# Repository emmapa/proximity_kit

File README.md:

# Proximity Kit

This repo contains the documentation of the following projects:

* PK_RC552, developed as part of deliverable for the prject [MUV](https://muv2020.eu)

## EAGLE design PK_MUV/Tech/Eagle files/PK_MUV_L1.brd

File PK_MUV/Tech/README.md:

# Parts
The PK_MUV kit is a portable device made of the following parts and features:

* Mcu/WiFi: Adafruit Feather HUZZAH esp8266 board
* NFC Reader: RC522 NFC reader
* Visual feedback: 3 WS1282 LEDs
* Audio feedback: buzzer
* Power switch
* Reset button
* Configuration button
* Indicator RGB Led for battery status
* Indicator RGB Led for configuration mode
* Indicator RGB Led for feedback
* Power supply: rechargeable battery or micro USB cable
* 6 mounting holes

The PK_MUV uses two off-the-shelf boards, the Adafruit Feather HUZZAH esp8266 and the NFC reader RC522, and four boards made in the fablab, the PK_MUV pcb, the PK_MUV_L1 pcb, the PK_MUV_L2 pcb and the PK_MUV_sw pcb.

The boards are made using the small milling machine Roland Modela MDX-20, each pcbs require two jobs: mill the trace and cut/drill the boards, in the folder digital files you find the png machinable files.
Tools used:
- one side copper plate, FR1
- to mill the traces: endmill, 0,4mm diameter
- to cut and drill: endmill, 1/64 inch diameter

The files used on the machine are in the folder [Machinable files](https://github.com/emmapa/proximity_kit/tree/master/PK_MUV/Tech/Machinable%20files).<br>
The original Eagle files are in the [Eagle files](https://github.com/emmapa/proximity_kit/tree/master/PK_MUV/Tech/Eagle%20files).

In Fablab Amsterdam the software to generate the rml file and send it to the machine is Fabmodules. It is highly recommended to use the last version of Fabmodules, aka mods http://mods.cba.mit.edu/; previous versions of fabmodules, still work but double check the output of the software before to send the job to the machine, in some cases the path is not well calculated.

In the image below you find the setting to envrage the traces and to drill holes/cut the board.
<br>

Note: when you mill the outlines, you will need to trick the fabmodules!! Some holes are two smalls to be identified with a diameter tool of 1/64inch (0.79248mm) so you can set the diameter tool to 0.78mm and all the holes will be milled; yes, you loos some copper on the pad but it is still enough to solder vias and components.

#### PK_MUV pcb

| top view  | bottom view |
| ------------- | ------------- |
|   |  |
| All the header are THT, pitch 2.54mm. <br> JP_LEDS: 1x3 female header, THT <br> JP_BUZ: holes for piezo<br> JP_SW: 2x2 male header<br> Feather header 1: 1x16 female header<br> Feather header 2: 1x16 female header<br> JP_LED_TAG: 1x4 female header<br> JP_NFC: 1x8 female header <br> | All the resistors are smd 1206. <br>R1: 1M Ohm<br> R2: 220k Ohm<br> R3: 0 Ohm<br> R4: 0 Ohm<br> R5: 10k Ohm<br> R6: 470 Ohm <br> R7: 0 Ohm<br>|
|   | |
|| 

**note**: the red traces are jumper wires placed on the top layer

#### PK_MUV_L1 pcb

| top view  | bottom view |
| ------------- | ------------- |
|   |  |
| The header is THT, pitch 2.54mm. <br> JP1: 1x04 male header 90° | Capacitors is smd 1206. <br>C1: 0.1uF <br> U1: WS2812B Led|
|   | |
|   | |

#### PK_MUV_L2 pcb

| top view  | bottom view |
| ------------- | ------------- |
|   |  |
| The header is THT, pitch 2.54mm. <br> JP1: 1x03 male header 90°   | Resistors and capacitors are smd 1206. <br>C1=C2: 0.1uF <br> U1=U2: WS2812B Led |
|   | |
|   | |

#### PK_MUV_sw pcb

| top View  | bottom view |
| ------------- | ------------- |
|   |  |
| sw1 = sw2: Tactile Switch THT | The header is smd, pitch 2.54mm <br> JP1: 2x2 male header<br> |
|   | |
||  |

#### Battery cable

#### Assembly note

#### BOM notes
Many items in the BOM can be bought only in minimum amount, when you actually are going to use one or two component. The total cost is therefore expressed as:
* total purchase: the cost of the purchase, buying the minimum amount per items
* cost of 1 kit: considering the cost of only the component used in the kit.

for example: if you buy the "feather header 1" from Farnell, you have to buy 10 components even if you are going to use only one. In the purchase cost the item "feather header 1" is 12€ but in the single cost of one kit, the item value is 1,2€.

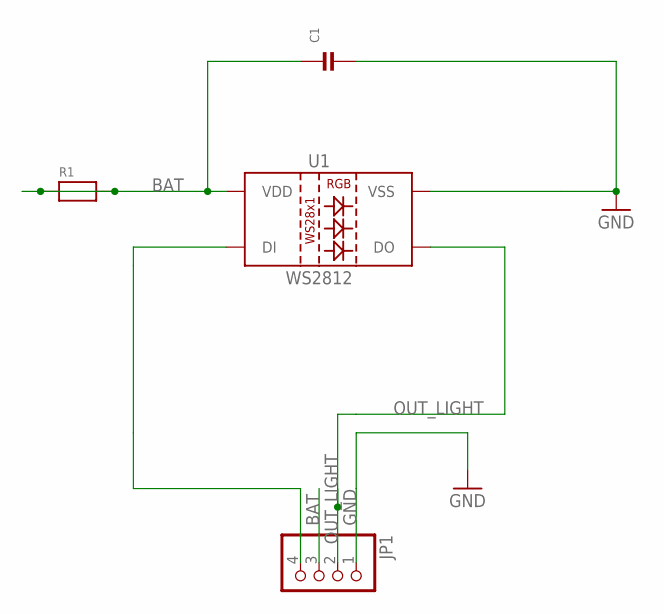
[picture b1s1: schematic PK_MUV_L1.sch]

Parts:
C1: CAP_CERAMIC1206; 1206
JP1: HEADER-1X4; 1X04_OVAL
R1: RESISTOR1206; 1206
U1: WS2812; LED-TRICOLOR-5050-IC

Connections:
BAT: C1.1, JP1.3, R1.1, R1.2, U1.3 (VDD), U1.5 (VDD)
GND: C1.2, JP1.1, U1.6 (VSS)
IN_LIGHT: JP1.4, U1.2 (DI)
OUT_LIGHT: JP1.2, U1.1 (DO)

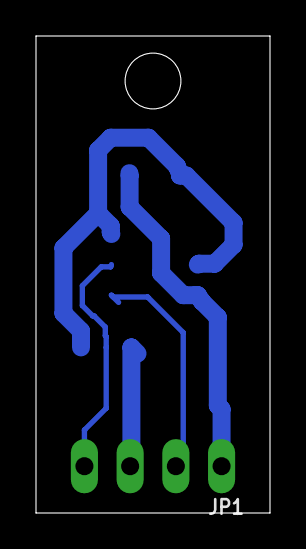
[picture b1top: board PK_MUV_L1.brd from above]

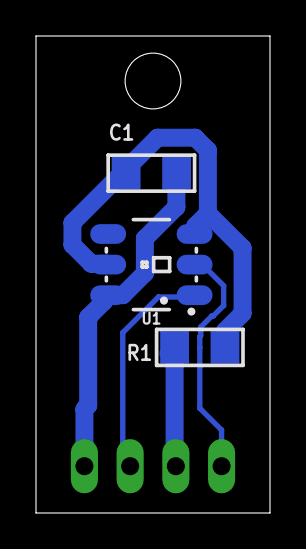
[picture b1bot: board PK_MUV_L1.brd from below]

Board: 2 copper layers, 13.0 x 26.5 mm, 4 parts (3 on the bottom side), 4 nets.

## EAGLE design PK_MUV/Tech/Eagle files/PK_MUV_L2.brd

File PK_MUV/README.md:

# PK_MUV

This page contains the description of the PK_MUV kit and the instructions to use it.<br>
In the Repo you also find:
* blocks diagram
* digital files to reproduce it, Eagle file and png files
* code
* BOM

The kit described in this Repo is about the electronics components and the firmware to realise the PK_MUV.

## Intro
The goal of the kit is to enable users of the application MUV, to identify proximity to strategic locations or routes, where the PK_MUV is located. The detection of proximity uses NFC technology and the user must be in possession of a [Tag_MUV](MUV-Tags) to properly use this feature of the app.
The PK_MUV is the device where the user can register proximity and it can be located in places important for the MUV project, for example: schools, offices, shops, parks, public services.

The PK_MUV is a WiFi module (esp8266) with NFC reader (RC522).
The PK_MUV kit is programmed to read [Tag_MUV](MUV-Tags). When the user operates the TAG_MUV on PK_MUV kit, the following informations are sent to the MUV server:
* Tag_MUV UID to identify the user
* PK_MUV ID to identify the location of the kit.<br>

The kit includes:
- Power slide switch: to turn on/off the kit when it runs on battery
- Reset switch: to reset the kit while it is operating
- Config switch: it is used to enter in configuration mode or run the check routine.
- Tag Led: rgb Led that gives feedback when a tag is detected by the reader, also called Tag routine.
- Config Led: rgb Led that gives feedback during the start-up and the check routines.
- Batt Led: rgb Led that visualise the battery status.

### Connect the PK_MUV to the local WiFi
Turn on the PK_MUV (ON/OFF switch). If the kit is not connected to the WiFi, the Config Led is on/blue, the kit is ready to be connected and it creates a network named MUV.
At this point you need a smartphone/tablet or computer, join the network MUV.

|| |
| ------------- | ------------- |

Automatically on the device you are using (smartphone/tablet/computer) the configuration window will pop-up.

|| |
| ------------- | ------------- |

If the window doesn't appear, open a browser and go to the address: http://192.168.4.1/.

Clicking on Info, you can see the information related to the kit and find the PK_MUV kit ID that in the window is called Chip ID.

Clicking on Configure WiFi, you are in the right place to connect the kit to you local WiFi.

Select the WiFi and type the password.
In the tag "Insert address", write the location of the kit.

Click save and the kit will be now connected, the Config Led blinks green and you are ready to use the kit.
It is also possible to enter in configuration mode manually, see the below section [configuration mode](Configuration-Mode).

### Modes and Routines/Messages
The operation of the PK_MUV can be described by modes and routine.
The modes are conditions in which the kit is waiting for some actions from the users:
* **configuration mode**: the kit is waiting to be connected to the local WiFi
* **operation mode**: the kit is operating and waiting to detect a Tag_MUV

The routines are a set of actions that the kit executes when it is triggered:
* **start-up routine**: it happens when the kit is powered-on or reset
* **tag routine**: it happens when the kit detect a tag
* **check routine**: it happens when the user need to check the functionality of the kit
The
<br>

#### Configuration Mode
Led Config : <br>
The kit is in configuration mode when it is not connected to the Local WiFi. In configuration mode the Config Led is steady blue.
You can manually enter in configuration mode with the following steps: keep pushed the Config switch and reset the kit. Hold the Config switch until the Config Led turns blue, the PK_MUV can to connected to the local Wifi, see previous [section](Connect-the-PK-MUV-to-the-local-WiFi).

**note**: you can also use configuration mode to change the WiFi Network at which the PK_MUV is connected.

#### Operation Mode
Config Led: <br>
If the kit has been successfully configured, it enters in operation mode.
The Tag Led and the Config Led are off, the NFC reader is ready to accept tags and the WiFi module is off to optimise the power consumption.
When the kit is operating and it has not been triggered by any tag, it will stay in operation mode.

#### Start-up routine
Config Led: <br>
When the kit is powered-on or reseted, it runs a sequence of test to verify that the proper functionality.
It will connect to the local WiFi, it will verify the connection with the server MUV and it will send a start-up message. If the execution of the start-up routine is successful the Config Led blinks green light and the start-up message is sent to the MUV server:

{"message":"startup","id":1756474,"location":"Nieuwmarkt 4, Amsterdam","rssi":-52, "batt":50}

for details about the payload content, see [Uplinks](Uplinks).

#### Tag Routine
Tag Led : <br>
When the reader get a Tag_MUV, the Tag Led blinks three times, meaning:
* the kit received a tag and the tag is recognised as Tag_MUV
* the kit connected to the local WiFi
* the kit sent the MUV message to the MUV server

and the kit will send to the MUV the following payload:

{"id":1756474,"uid":"04:23:AB:32:EC:4C:81”}

for details about the payload content, see [Uplinks](Uplinks).

The color code of the Tag Led is:<br>
 : the tag doesn't have the credential of the MUV project.<br>
 : the tag was recognised as MUV, but the the kit couldn't connect to the WiFi.<br>
 : the tag was recognised as MUV, it could connect to the WiFi but it couldn't reach the MUV server.

#### Check Routine
To execute the check routine, press once the Config Switch and you can verify the following features:
* battery level
* WiFi connection
* MUV server connectivity

The Batt Led will be steady for few seconds and the colour represents the battery level.<br>
The feedback of the routine is visualised on the Config Led:<br>
: the kit is operating properly and it will send the "check message".<br>
: the kit can't connect to the WiFi.<br>
: the kit can't reach the MUV server and the "check message" is not sent.

The message sent to the server is:<br>
{"message":"check","id":1756474,"location":"Funen","rssi":-59,"batt”:50}<br>
for details about the payload content, see below.

#### Uplinks
Depending by the triggered routines, the PK_MUV send three different messages to the MUV server (MQTT protocol). The topic is prox and the payloads, Jason format, are the following:

{"message":"startup","id":1756474,"location":"Nieuwmarkt 4, Amsterdam","rssi":-52, "batt":50}<br>
{"id":1756474,"uid":"04:23:AB:32:EC:4C:81”}<br>
{"message":"check","id":1756474,"location":"Nieuwmarkt 4, Amsterdam","rssi":-59,"batt”:50}<br>

messagge: triggered routine , start-up or check <br>
id: chipID or PK_MUV ID <br>
uid: Tag UID <br>
location: location of the kit, to be inserted during configuration mode <br>
rssi: rssi <br>
batt: battery level in % <br>

## Power supply and Batt Led
The PK_MUV kit runs on a rechargeable battery, a 2000mAh Lithium Ion Polymer cell last about 4 days when the PK_MUV kit works in operational mode. The status of the battery is visualised by the Batt Led:

* battery level >= 96%: Batt Led is steady on, green
* 96% > battery level >= 80%: Batt Led blinks slow, colour green
* 80% > battery level >= 60%: Batt Led blinks, colour green/yellow
* 60% > battery level >= 40%: Batt Led blinks, colour yellow.
* 40% > battery level >= 20%: Batt Led blinks, colour orange.
* 20% > battery level >= 10%: Batt Led blinks, colour red.
* battery level < 10%: Batt Led is steady on, colour red.

When the Batt Led is red, the battery is almost empty. To recharge the internal battery you can use a micro USB cable and a +5V USB charger (the ones you use with phones are good), plug the cable to the USB port on the side of the kit. When the Batt Led is steady green, the battery is charged. While the kit is under charge it, it still operates normally.

**Note**: when you charge the battery, be sure the power switch is ON otherwise the battery will not get charged.

You can run the PK_MUV kit without battery and use the USB cable to supply it. In this case it is recommended to disconnect the battery or leave the power switch in position OFF.
**Note**: when the USB cable is plugged, the kit operated continuously.

## MUV Tags
The Tags that have been successfully tested are NTAG2013 and NTAG203, they are manufactured in different shapes: key-chain, sticker, business card and bracelet.
To be able to use a Tag with the PK_MUV kit, you have to write in the Tag the MUV password and transform it in a Tag_MUV. On [this page](https://www.wakdev.com/en/apps.html) you find a list of apps to write NFC Tags but you also need a device to actually write the tag; in some cases the phone can do the job but in some other cases, for example if you have an iPhone6, you have to adopt an external device. During the testing phase of the PK_MUV, the ACR122 writer has been used with the desktop version of the software NFC tools.

How to use the ACR122 with NFC tools: [link](https://www.wakdev.com/en/apps/nfc-tools-pc-mac.html) To have access to the key, see section [Contacts](Contacts).

## Troubleshooting
| Problem | Solution |
|---------| -------- |
| Config Led is on: purple <br> | The FS are formatted and The WiFi settings reseted. <br> The Feather esp8266 must be reprogrammed.  <br>See [Code](code) page. |
| Config Led is on: aqua <br> | The MUV server can't be reached. <br> Reset the Kit. <br> Check the MUV credentials saved in the code |
| Config Led is on: blue <br>  | The kit is in Configuration mode.<br> Ready to be connected to the Local WiFi: [how](#Connect-the-PK-MUV-to-the-local-WiFi)  |

## Contacts
To have access to the MUV password, please contact: XXX

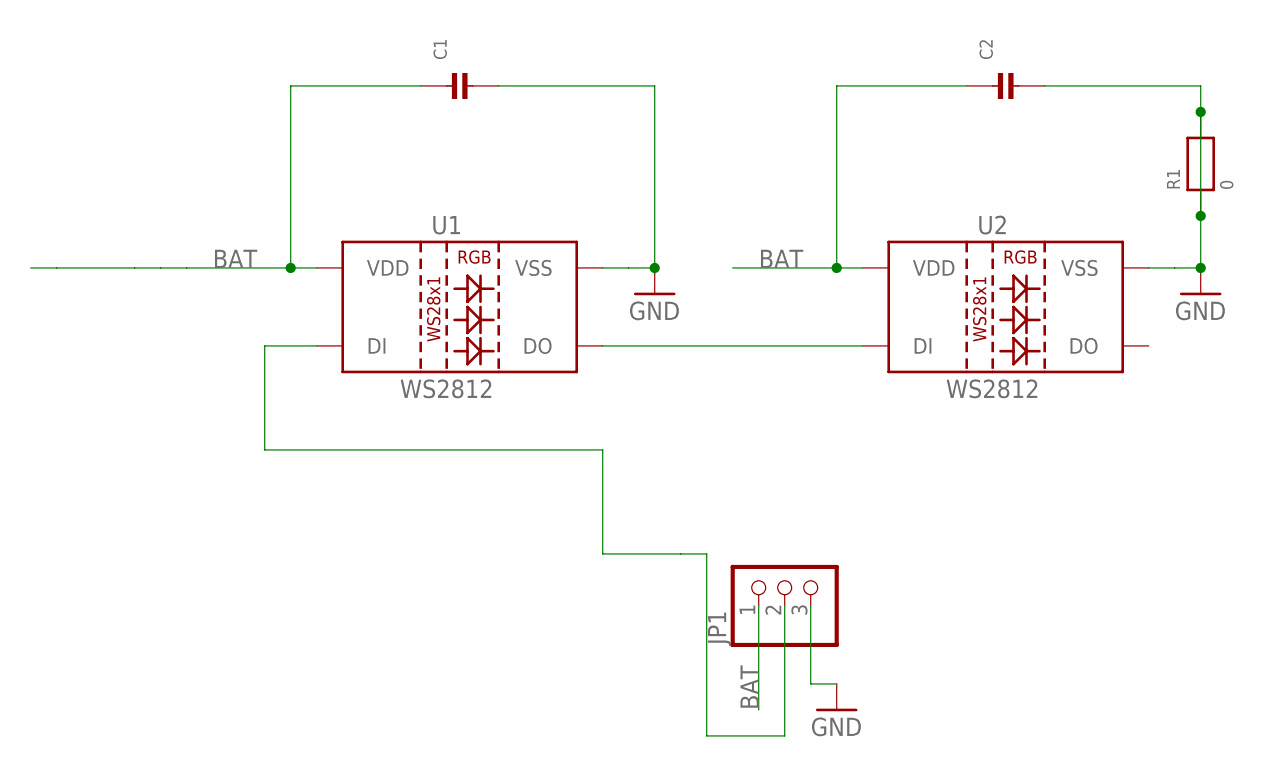
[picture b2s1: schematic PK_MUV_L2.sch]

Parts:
C1, C2: CAP_CERAMIC1206; 1206
JP1: HEADER-1X3; 1X03_OVAL
R1: 0; 1206
U1, U2: WS2812; LED-TRICOLOR-5050-IC

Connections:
BAT: C1.1, C2.1, JP1.1, U1.3 (VDD), U1.5 (VDD), U2.3 (VDD), U2.5 (VDD)
GND: C1.2, C2.2, JP1.3, R1.1, R1.2, U1.6 (VSS), U2.6 (VSS)
unnamed: JP1.2, U1.2 (DI)
unnamed: U1.1 (DO), U2.2 (DI)

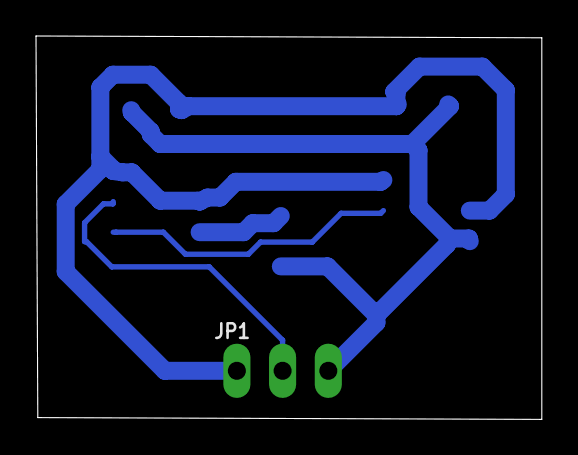
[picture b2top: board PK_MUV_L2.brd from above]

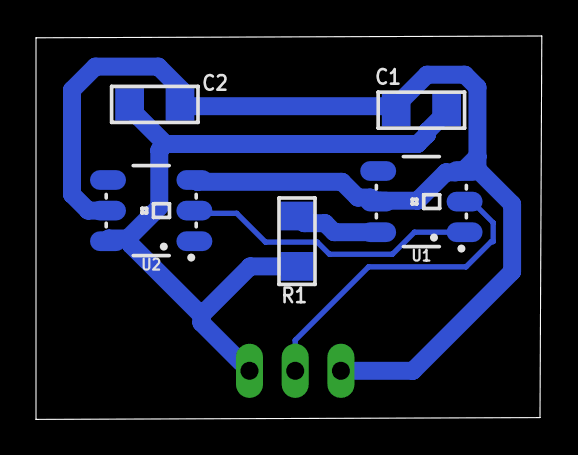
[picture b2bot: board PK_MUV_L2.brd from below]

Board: 2 copper layers, 28.1 x 21.3 mm, 6 parts (5 on the bottom side), 4 nets.

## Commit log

2018-11-30 Rename read.md to README.md
2018-12-02 Update tech
2019-03-18 png L1
2019-03-19 update hardware page
2019-03-19 update images config

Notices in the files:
parts and their libraries:
SparkFun-LED: Licensing: Creative Commons ShareAlike 4.0 International - https://creativecommons.org/licenses/by-sa/4.0
microbuilder: This work is placed in the public domain, and may be freely used for commercial and non-commercial work with the following conditions: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
